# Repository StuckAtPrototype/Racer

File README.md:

# Micro Racer Car - StuckAtPrototype

*thank you for the overwhelmingly positve support!! such an inspiration to keep making fun open source content!*

## New Youtube video about improvements 
Lots of new improvements and I am now selling a kit for these! Check out the video here:
https://www.youtube.com/watch?v=FulhEs5R5WU

## Original Youtube Video
A bit of a back-story of how this project came to be. 

Sub if you like what you see.

*Some pictures of the project*

## Hardware Remote for this car

https://github.com/StuckAtPrototype/Thumbtroller

## Project Structure
The project consists of
1. Firmware
2. Hardware
3. Mechanical 
4. Scripts

These are structured into their own files. I could have used submodules, but decided against it.  

### 1. Firmware
Code for the little car. This lives on the ESP32

#### Requirements
- ESP32 IDF version 5.3.1
- USB to Serial dongle
- Target set to ESP32-H2

### 2. Hardware

#### Schematic
PDF schematic included for your viewing pleasure. 
#### PCBs
All the gerber files you'd need to send to a fab house. 
#### Kicad
All the files you'd need to expand and work on this further. If you'd like. 

### 3. Mechanical

#### Enclosure
All the step files you need to make one of these. Extrusion printer works well for this part.  

#### Wheels
A bit of caution on this one.. you'll need an SLA printer. 

### 4. Scripts
Did anyone say neural networks? 

This folder has all the python code you'd need to train up your own neural network for the car. It also consists scripts that let you drive it using a keyboard -- just in case you dont want to make a physical controller.  

#### Requirements
- Python 3
- You'll need to install a bunch of pip modules 

#### Training the neural network
Training the neural network is as simple as running the training script with the data in the `color_data.txt` file. For data format see the sample data in the file. You need to stick to the formatting. 

To train run `python trainer.py`

#### Keyboard controller
To run the script `python controller.py`

Use `w` `s` `a` `d` for control. Modify the script for different speeds, etc

*Protocol for motor control* 

60,1,60,1,5 -- translates to:

motor side A: speed 60, direction forward

motor side B: speed 60, direction forward

500 miliseconds run time

See firmware file `motor.c` if you need more details

## What the project could use
1. Cleanup, but thats true for almost anything out there
2. Some fun code that makes the little car drive using the color sensor -- think very fancy line follower
3. LLM integration -- ChatGPT driving a physical little robot? anyone? :)

## If you take it further
Let me know if you ever make one of these, I'd love to see it. Seriously, that'd be exciting and inspiring to keep making my projects open source!

---
## License
### Apache 2.0 -- i.e. use as you'd like
http://www.apache.org/licenses/LICENSE-2.0

--- 
## Special Thanks
Thanks to Michael Angerer for his open sourced `esp32_ble_ota` project. I used it to get BLE running in this project. His blog post and github repo are a great resource. Check it out. https://github.com/michael-angerer/esp32_ble_ota

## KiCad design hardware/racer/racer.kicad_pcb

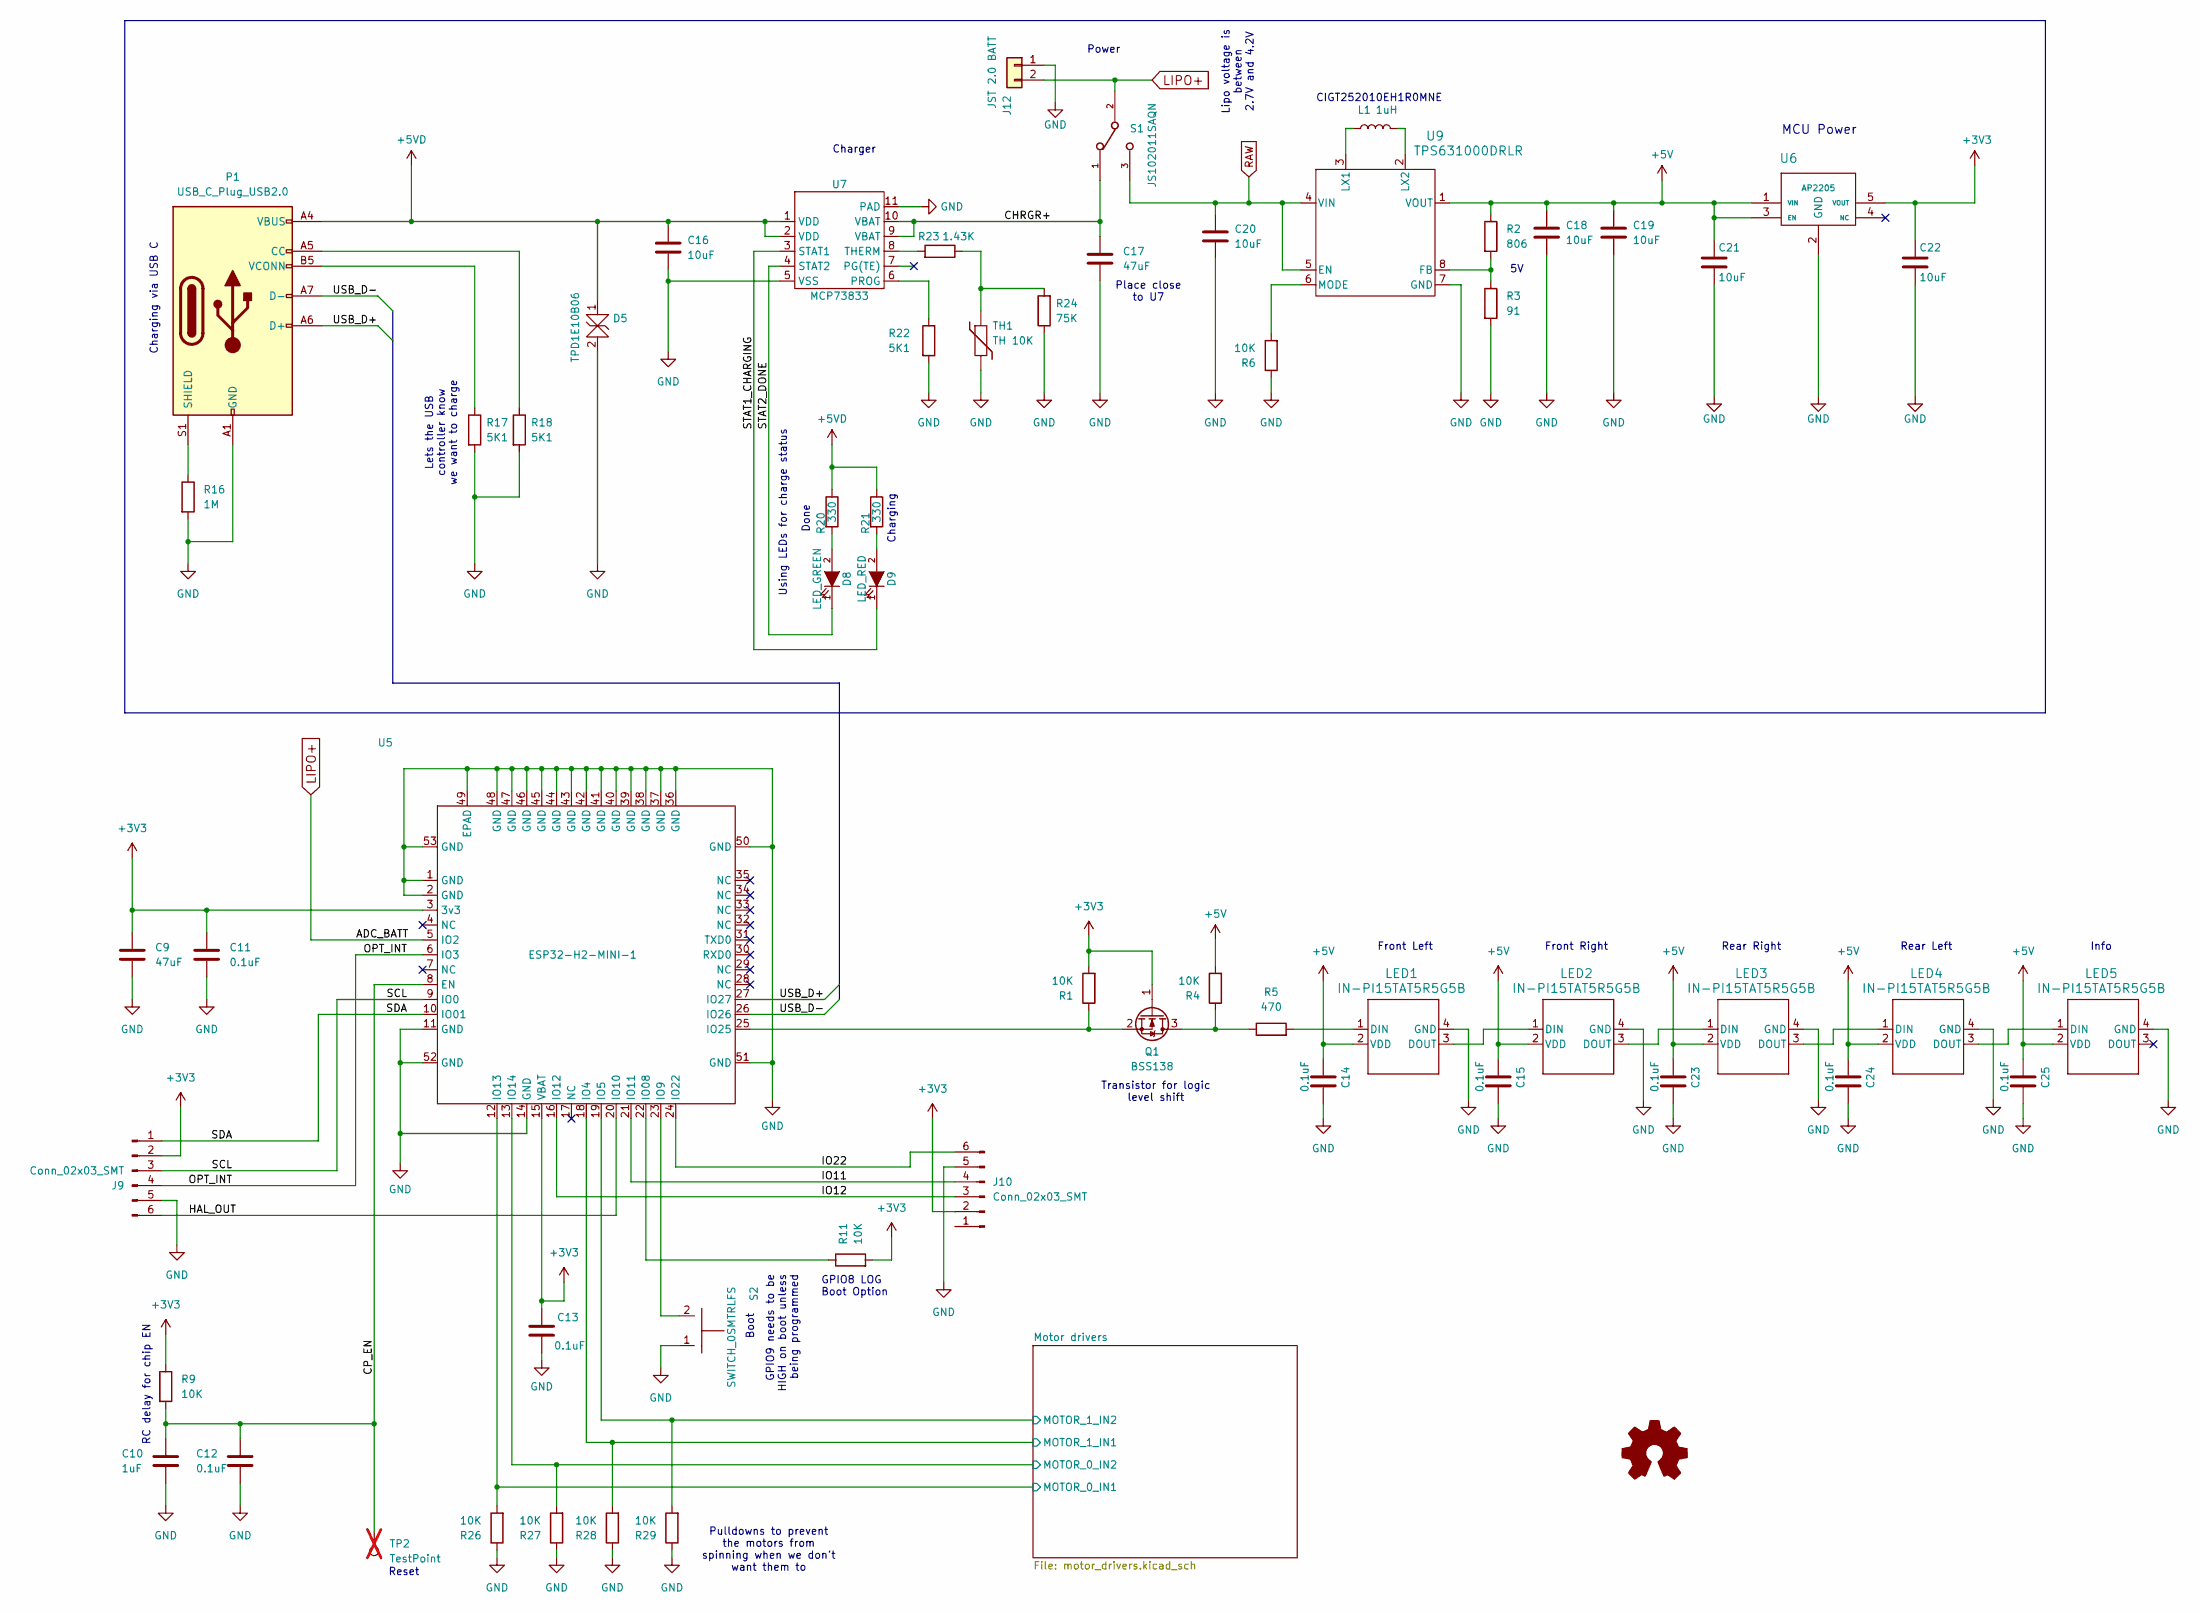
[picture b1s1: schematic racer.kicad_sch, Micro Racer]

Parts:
C9, C17: 47uF; C_0603_1608Metric
C10: 1uF; C_0603_1608Metric
C11, C12, C13, C14, C15, C23, C24, C25: 0.1uF; C_0603_1608Metric
C16, C18, C19, C20, C21, C22: 10uF; C_0603_1608Metric
D5: TPD1E10B06; D_SOD-523
D8: LED_GREEN; C_0603_1608Metric
D9: LED_RED; C_0603_1608Metric
J9, J10: Conn_02x03_SMT; PinHeader_2x03_P1.27mm_Vertical_SMD
J12: JST 2.0 BATT; JST_PH_B2B-PH-K_1x02_P2.00mm_Vertical
L1: 1uH; RES_CIGT252010
LED1, LED2, LED3, LED4, LED5: IN-PI15TAT5R5G5B; IN-PI15_INL
P1: USB_C_Plug_USB2.0; GCT_USB4105-GF-A
Q1: BSS138; SOT-23
R1, R4, R6, R9, R11, R26, R27, R28, R29: 10K; R_0603_1608Metric
R2: 806; R_0603_1608Metric
R3: 91; R_0603_1608Metric
R5: 470; R_0603_1608Metric
R16: 1M; R_0603_1608Metric
R17, R18, R22: 5K1; R_0603_1608Metric
R20, R21: 330; R_0603_1608Metric
R23: 1.43K; R_0603_1608Metric
R24: 75K; R_0603_1608Metric
S1: JS102011SAQN; SW_JS102011SAQN
S2: SWITCH_0SMTRLFS
TH1: TH 10K; R_0603_1608Metric
TP2: TestPoint; TestPoint_Pad_1.5x1.5mm; not fitted
U5: ESP32-H2-MINI-1; MODULE_ESP32-H2-MINI-1-H2
U6: AP2205; AP2204
U7: MCP73833; SON50P300X300X100-11N
U9: TPS631000DRLR; TPS631000DRLR_TEX

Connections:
+3V3: C9.1, C11.1, C13.1, C22.1, J9.2, J10.2, Q1.1 (G), R1.2, R9.1, R11.2, U5.3 (3v3), U5.15 (VBAT), U6.5 (VOUT)
+5V: C14.1, C15.1, C18.1, C19.1, C21.1, C23.1, C24.1, C25.1, LED1.2 (VDD), LED2.2 (VDD), LED3.2 (VDD), LED4.2 (VDD), LED5.2 (VDD), R2.1, R4.2, U6.1 (VIN), U6.3 (EN), U9.1 (VOUT)
+5VD: C16.1, D5.1, P1.A4 (VBUS), P1.A9 (VBUS), P1.B4 (VBUS), P1.B9 (VBUS), R20.1, R21.1, U7.1 (VDD), U7.2 (VDD)
/CHRGR+: C17.1, S1.1, U7.9 (VBAT), U7.10 (VBAT)
/CP_EN: C10.1, C12.1, R9.2, TP2.1, U5.8 (EN)
/HAL_OUT: J9.6, U5.20 (IO10)
/IO11: J10.4, U5.21 (IO11)
/IO12: J10.3, U5.16 (IO12)
/IO22: J10.6, U5.24 (IO22)
/OPT_INT: J9.4, U5.6 (IO3)
/SCL: J9.3, U5.9 (IO0)
/SDA: J9.1, U5.10 (IO01)
/STAT1_CHARGING: D9.1 (K), U7.3 (STAT1)
/STAT2_DONE: D8.1 (K), U7.4 (STAT2)
/USB_D+: P1.A6 (D+), U5.27 (IO27)
/USB_D-: P1.A7 (D-), U5.26 (IO26)
GND: C9.2, C10.2, C11.2, C12.2, C13.2, C14.2, C15.2, C16.2, C17.2, C18.2, C19.2, C20.2, C21.2, C22.2, C23.2, C24.2, C25.2, D5.2, J9.5, J10.5, J12.1, LED1.4 (GND), LED2.4 (GND), LED3.4 (GND), LED4.4 (GND), LED5.4 (GND), P1.A1 (GND), P1.A12 (GND), P1.B1 (GND), P1.B12 (GND), R3.2, R6.1, R16.2, R17.2, R18.2, R22.2, R24.1, R26.1, R27.1, R28.1, R29.1, S2.1, TH1.2, U5.1 (GND), U5.2 (GND), U5.11 (GND), U5.14 (GND), U5.36 (GND), U5.37 (GND), U5.38 (GND), U5.39 (GND), U5.40 (GND), U5.41 (GND), U5.42 (GND), U5.43 (GND), U5.44 (GND), U5.45 (GND), U5.46 (GND), U5.47 (GND), U5.48 (GND), U5.49 (EPAD), U5.50 (GND), U5.51 (GND), U5.52 (GND), U5.53 (GND), U6.2 (GND), U7.5 (VSS), U7.11 (PAD), U9.7 (GND); also elsewhere on the board
LIPO+: J12.2, S1.2, U5.5 (IO2)
MOTOR_0_IN1: R26.2, U5.12 (IO13); also elsewhere on the board
MOTOR_0_IN2: R27.2, U5.13 (IO14); also elsewhere on the board
MOTOR_1_IN1: R28.2, U5.18 (IO4); also elsewhere on the board
MOTOR_1_IN2: R29.2, U5.19 (IO5); also elsewhere on the board
unnamed: D8.2 (A), R20.2
unnamed: D9.2 (A), R21.2
unnamed: LED1.1 (DIN), R5.2
unnamed: LED1.3 (DOUT), LED2.1 (DIN)
unnamed: LED2.3 (DOUT), LED3.1 (DIN)
unnamed: LED3.3 (DOUT), LED4.1 (DIN)
unnamed: LED4.3 (DOUT), LED5.1 (DIN)
unnamed: P1.A5 (CC), R18.1
unnamed: P1.S1 (SHIELD), R16.1
unnamed: P1.B5 (VCONN), R17.1
unnamed: Q1.3 (D), R4.1, R5.1
unnamed: Q1.2 (S), R1.1, U5.25 (IO25)
unnamed: R23.1, R24.2, TH1.1
unnamed: R11.1, U5.22 (IO08)
unnamed: S2.2, U5.23 (IO9)
unnamed: R22.1, U7.6 (PROG)
unnamed: R23.2, U7.8 (THERM)
unnamed: R2.2, R3.1, U9.8 (FB)
unnamed: L1.1, U9.3 (LX1)
unnamed: L1.2, U9.2 (LX2)
unnamed: R6.2, U9.6 (MODE)
RAW: C20.1, S1.3, U9.4 (VIN), U9.5 (EN); also elsewhere on the board

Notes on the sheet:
Lipo voltage is between 2.7V and 4.2V
Charging via USB C
Using LEDs for charge status
RC delay for chip EN
Lets the USB controller know we want to charge
Front Right
Power
Rear Right
Reset
GPIO9 needs to be HIGH on boot unless being programmed
Pulldowns to prevent the motors from spinning when we don't want them to
Charger
GPIO8 LOG Boot Option
Charging
Done
Info
MCU Power
Front Left
CIGT252010EH1R0MNE
Rear Left
Place close to U7
Boot
Transistor for logic level shift

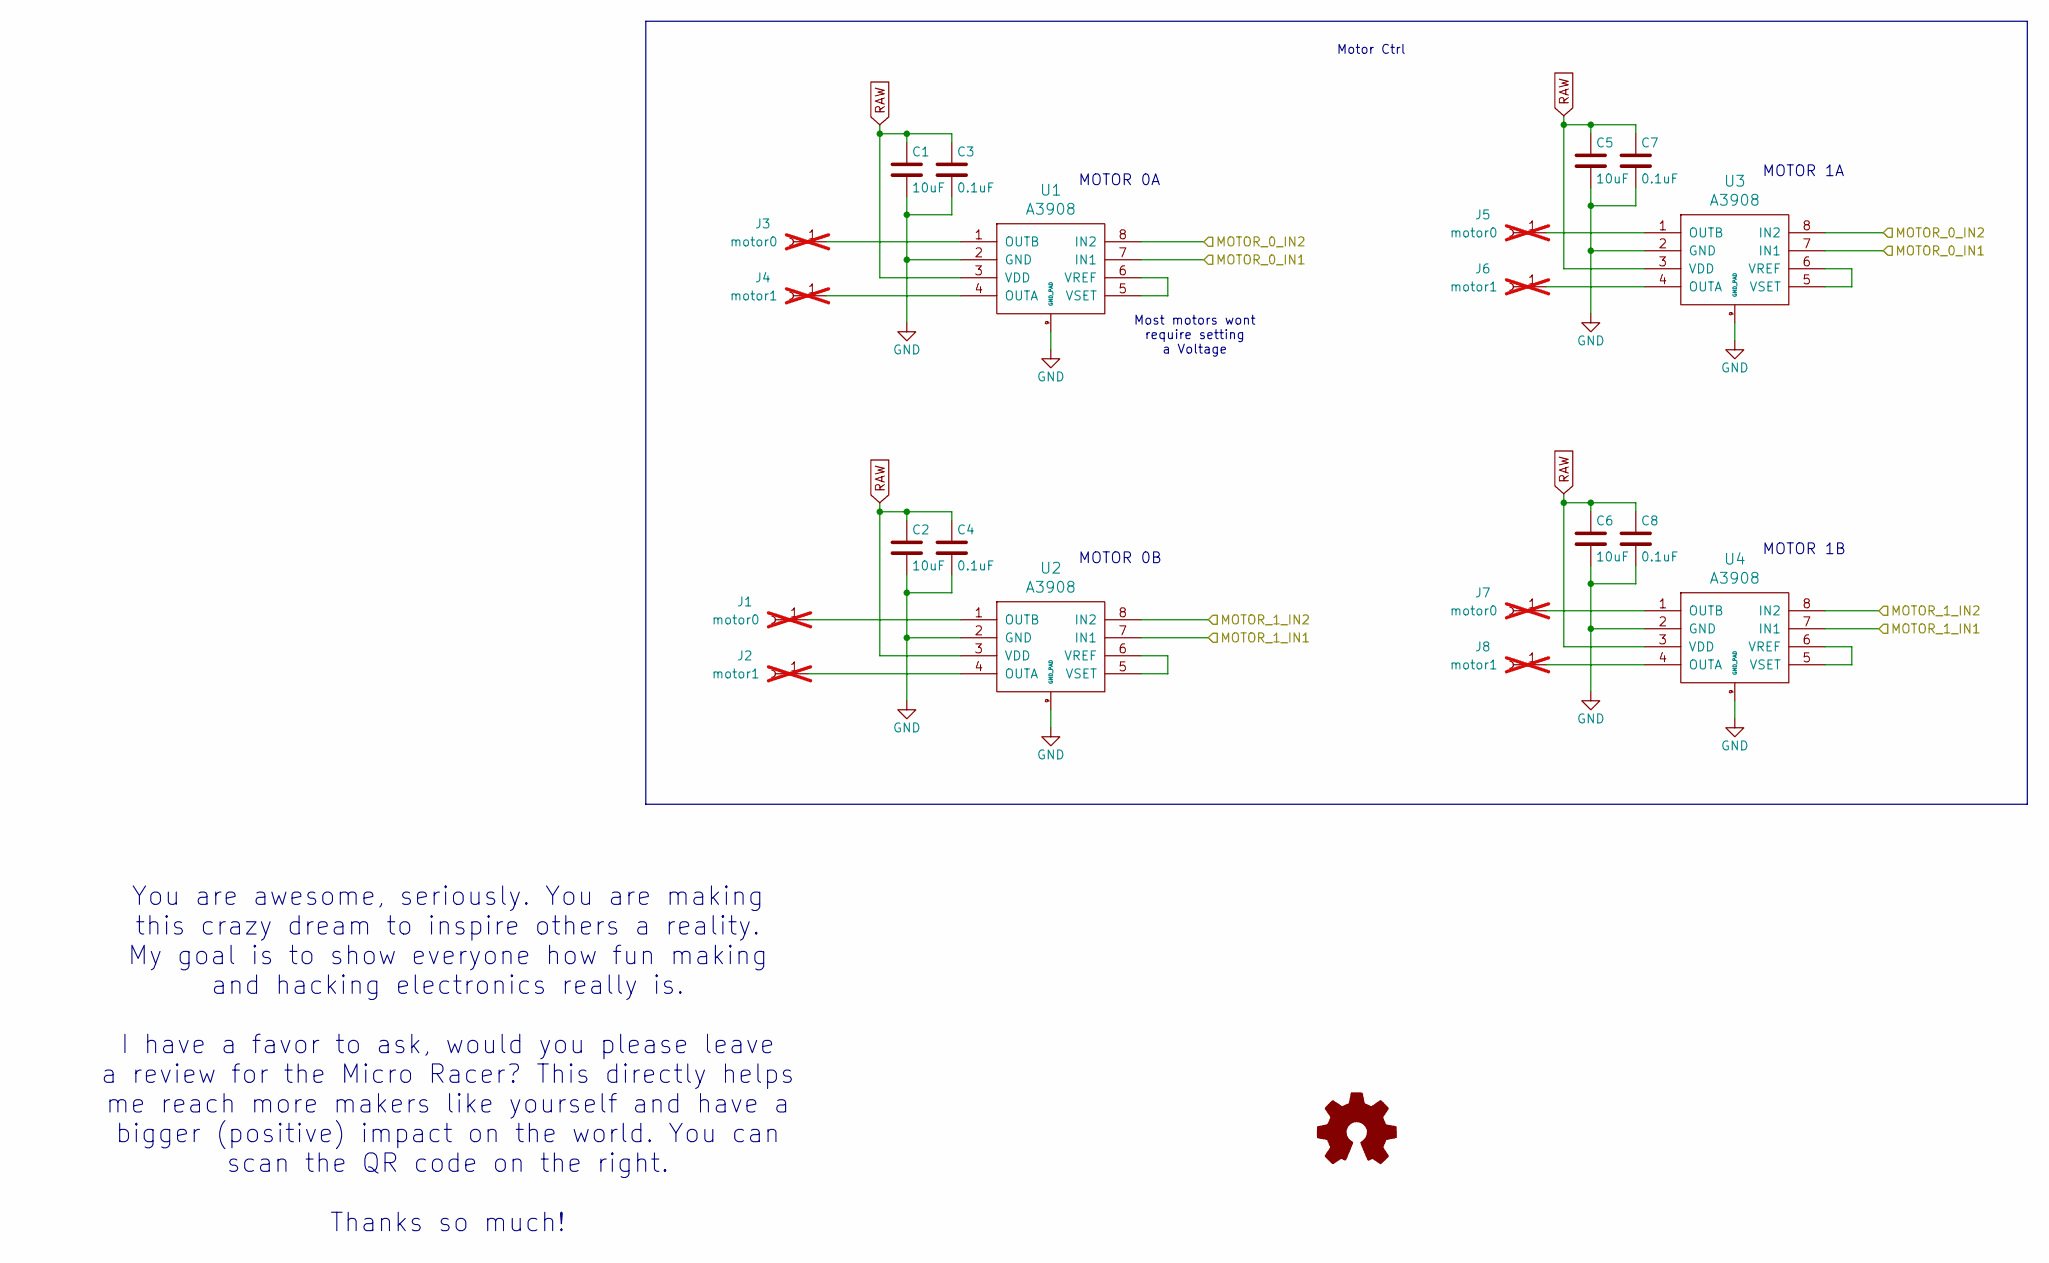
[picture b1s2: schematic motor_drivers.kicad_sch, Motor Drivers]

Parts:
C1, C2, C5, C6: 10uF; C_0603_1608Metric
C3, C4, C7, C8: 0.1uF; C_0603_1608Metric
J1, J3, J5, J7: motor0; TestPoint_Pad_2.0x2.0mm; not fitted
J2, J4, J6, J8: motor1; TestPoint_Pad_2.0x2.0mm; not fitted
U1, U2, U3, U4: A3908

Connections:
GND: C1.2, C2.2, C3.2, C4.2, C5.2, C6.2, C7.2, C8.2, U1.2 (GND), U1.9 (GND_PAD), U2.2 (GND), U2.9 (GND_PAD), U3.2 (GND), U3.9 (GND_PAD), U4.2 (GND), U4.9 (GND_PAD); also elsewhere on the board
MOTOR_0_IN1: U1.7 (IN1), U3.7 (IN1); also elsewhere on the board
MOTOR_0_IN2: U1.8 (IN2), U3.8 (IN2); also elsewhere on the board
MOTOR_1_IN1: U2.7 (IN1), U4.7 (IN1); also elsewhere on the board
MOTOR_1_IN2: U2.8 (IN2), U4.8 (IN2); also elsewhere on the board
unnamed: J1.1, U2.1 (OUTB)
unnamed: J2.1, U2.4 (OUTA)
unnamed: J3.1, U1.1 (OUTB)
unnamed: J4.1, U1.4 (OUTA)
unnamed: J5.1, U3.1 (OUTB)
unnamed: J6.1, U3.4 (OUTA)
unnamed: J7.1, U4.1 (OUTB)
unnamed: J8.1, U4.4 (OUTA)
unnamed: U1.5 (VSET), U1.6 (VREF)
unnamed: U2.5 (VSET), U2.6 (VREF)
unnamed: U3.5 (VSET), U3.6 (VREF)
unnamed: U4.5 (VSET), U4.6 (VREF)
RAW: C1.1, C2.1, C3.1, C4.1, C5.1, C6.1, C7.1, C8.1, U1.3 (VDD), U2.3 (VDD), U3.3 (VDD), U4.3 (VDD); also elsewhere on the board

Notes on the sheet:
Most motors wont require setting a Voltage
You are awesome, seriously. You are making this crazy dream to inspire others a reality. My goal is to show everyone how fun making and hacking electronics really is. I have a favor to ask, would you please leave a review for the Micro Racer? This directly helps me reach more makers like yourself a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
MOTOR 1B
MOTOR 0A
Motor Ctrl
MOTOR 1A
MOTOR 0B

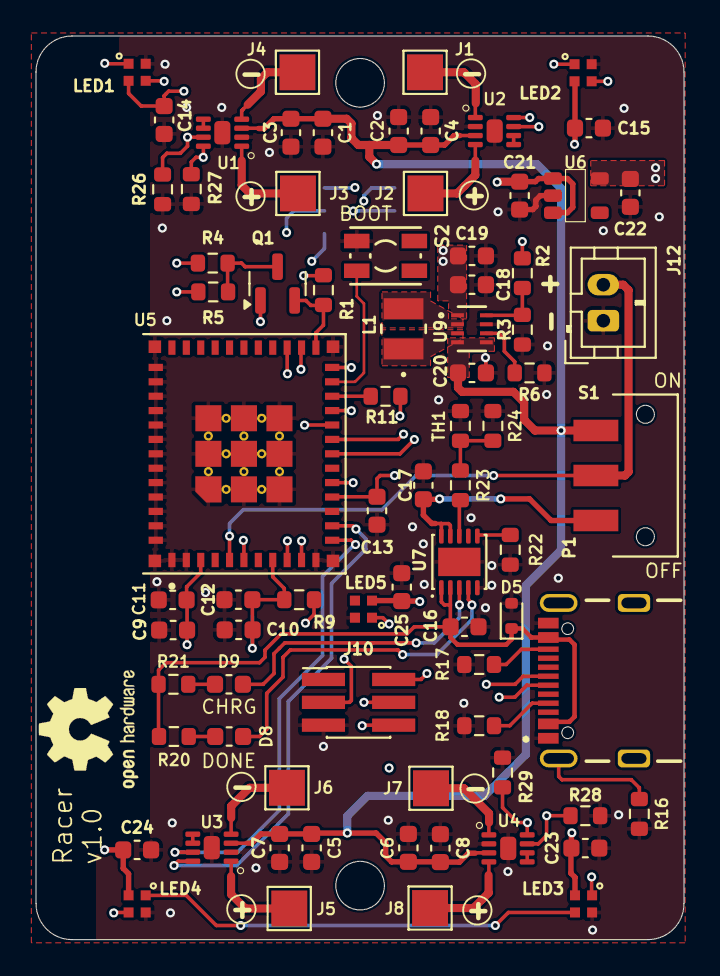
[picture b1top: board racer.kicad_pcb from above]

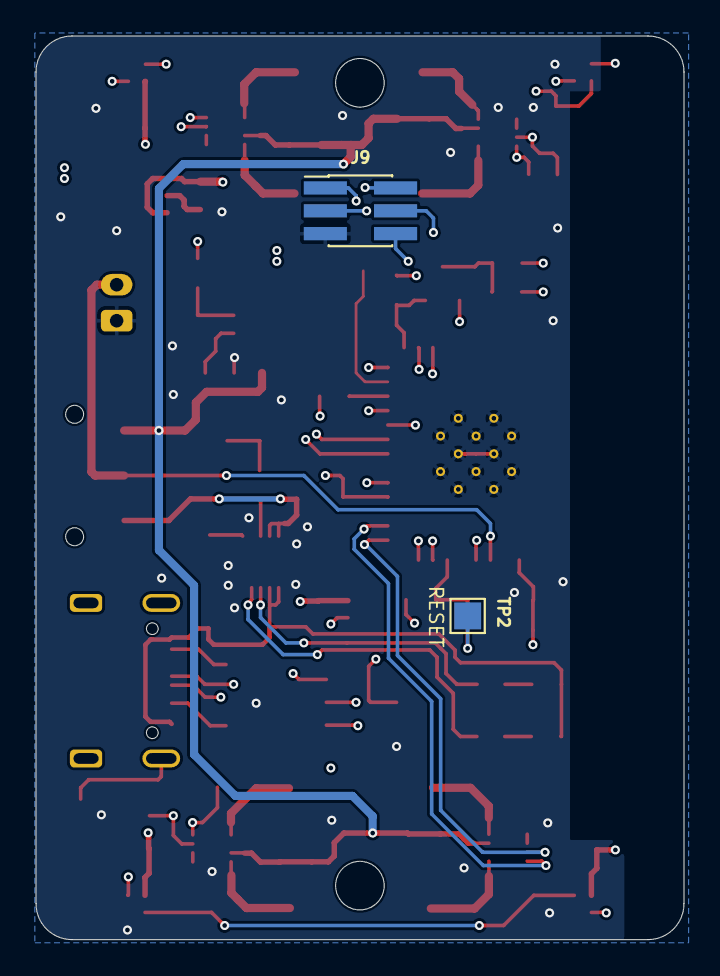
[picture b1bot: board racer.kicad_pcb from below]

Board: 4 copper layers, 36.0 x 50.2 mm, 79 parts (2 on the bottom side), 56 nets.

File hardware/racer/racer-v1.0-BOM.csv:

Designator,Quantity,Manufacturer Part Number,Package/Footprint,Description
U9,1,TPS631000DRLR,TPS631000DRLR_TEX,TPS631000DRLR
"R6,R26,R28,R29,R9,R1,R27,R11,R4",9,WR06X103 JTL,R_0603_1608Metric,10K
"C2,C16,C20,C18,C5,C6,C19,C1,C22",9,GRM188R61A106ME69D,C_0603_1608Metric,10uF
S2,1,RKB2SJK250SMTR LFS,SWITCH_0SMTRLFS,SWITCH_0SMTRLFS
"C7,C12,C13,C24,C15,C3,C8,C14,C4,C23,C11,C25",12,CC0603KRX7R7BB104,C_0603_1608Metric,0.1uF
R2,1,RQ73C1J806RBTDF,R_0603_1608Metric,806
U6,1,AP2205-33W5-7,AP2204,AP2205
R23,1,RT0603BRE071K43L,R_0603_1608Metric,1.43K
J9,1,GRPB032VWQS-RC,PinHeader_2x03_P1.27mm_Vertical_SMD,Conn_02x03_SMT
Q1,1,BSS138,SOT-23,BSS138
D9,1,150060RS75000,C_0603_1608Metric,LED_RED
"R17,R22,R18",3,RC0603FR-075K1L,R_0603_1608Metric,5K1
"LED1,LED3,LED5,LED4,LED2",5,IN-PI15TAT5R5G5B,IN-PI15_INL,IN-PI15TAT5R5G5B
D8,1,150060GS75000,C_0603_1608Metric,LED_GREEN
"U4,U1,U2,U3",4,A3908EEETR-T,A3908,A3908
J12,1,B2B-PH-K-S,JST_PH_B2B-PH-K_1x02_P2.00mm_Vertical,JST 2.0 BATT
P1,1,USB4105-GF-A,GCT_USB4105-GF-A,USB_C_Plug_USB2.0
TH1,1,NTCG163JF103HT1,R_0603_1608Metric,TH 10K
U5,1,ESP32-H2-MINI-1,MODULE_ESP32-H2-MINI-1-H2,ESP32-H2-MINI-1
R3,1,CR0603-FX-91R0ELF ,R_0603_1608Metric,91
R5,1,ESR03EZPF4700,R_0603_1608Metric,470
L1,1,CIGT252010EH1R0MNE,RES_CIGT252010,1uH
C10,1,CC0603KRX5R8BB105,C_0603_1608Metric,1uF
"R21,R20",2,RC0603JR-07330RL,R_0603_1608Metric,330
D5,1,TPD1E10B06DYAR,D_SOD-523,TPD1E10B06
S1,1,JS102011SAQN,SW_JS102011SAQN,JS102011SAQN
R24,1,ERJ-PB3B7502V,R_0603_1608Metric,75K
U7,1,MCP73833T-AMI/MF,SON50P300X300X100-11N,MCP73833
C17,1,GRM188R60J226MEA0J,C_0603_1608Metric,22uF
R16,1,RMCF0603FT1M00,R_0603_1608Metric,1M
C9,1,GRM188C80E476ME05D,C_0603_1608Metric,47uF
C21,1,CL10A225KO8NNNC,C_0603_1608Metric,2.2uF

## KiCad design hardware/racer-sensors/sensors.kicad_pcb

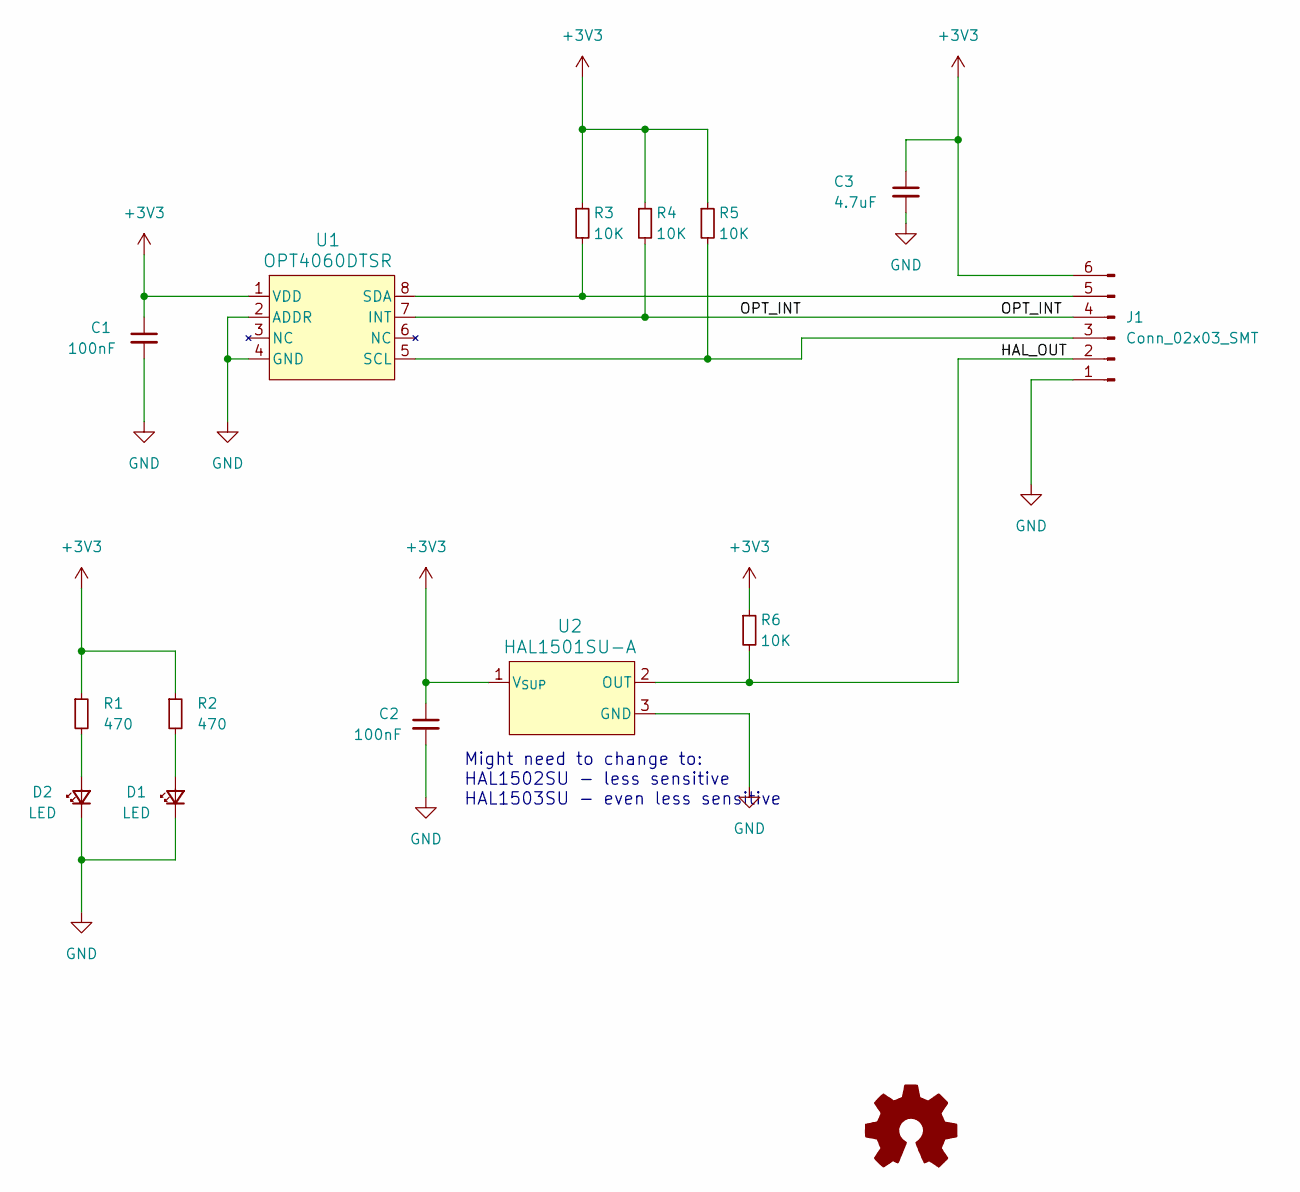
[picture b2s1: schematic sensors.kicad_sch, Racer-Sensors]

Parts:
C1, C2: 100nF; C_0603_1608Metric
C3: 4.7uF; C_0603_1608Metric
D1, D2: LED; LED_0603_1608Metric
J1: Conn_02x03_SMT; PinHeader_2x03_P1.27mm_Vertical_SMD
R1, R2: 470; R_0603_1608Metric
R3, R4, R5, R6: 10K; R_0603_1608Metric
U1: OPT4060DTSR; FCSOT8_DTS_TEX
U2: HAL1501SU-A; SOT-23_TO-236_TDK

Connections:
+3V3: C1.1, C2.1, C3.1, J1.6, R1.1, R2.1, R3.1, R4.1, R5.1, R6.1, U1.1 (VDD), U2.1 (VSUP)
/HAL_OUT: J1.2, R6.2, U2.2 (OUT)
/OPT_INT: J1.4, R4.2, U1.7 (INT)
/SCL: J1.3, R5.2, U1.5 (SCL)
/SDA: J1.5, R3.2, U1.8 (SDA)
GND: C1.2, C2.2, C3.2, D1.1 (K), D2.1 (K), J1.1, U1.2 (ADDR), U1.4 (GND), U2.3 (GND)
unnamed: D1.2 (A), R2.2
unnamed: D2.2 (A), R1.2

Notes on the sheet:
Might need to change to: HAL1502SU - less sensitive HAL1503SU - even less sensitive

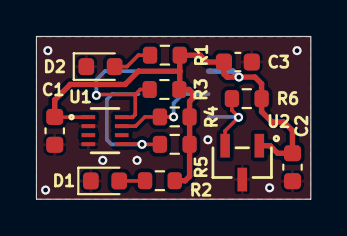
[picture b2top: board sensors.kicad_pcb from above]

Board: 4 copper layers, 15.2 x 9.0 mm, 14 parts (1 on the bottom side), 8 nets.

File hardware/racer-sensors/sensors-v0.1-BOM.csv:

Id,Designator,Footprint,Quantity,Designation,Supplier and ref,Notes
1,"R4,R5,R6,R3",R_0603_1608Metric,4,10K,WR06X103 JTL,
2,"D1,D2",LED_0603_1608Metric,2,LED,IN-S63AT5UW,
3,"R2,R1",R_0603_1608Metric,2,R,ESR03EZPF4700,"Note: I used a 470ohm resistor, but this might need to be adjusted to vary brightness "
4,C3,C_0603_1608Metric,1,4.7uF,GRM188R61A106ME69D,Replaced with 10uF
5,"C1,C2",C_0603_1608Metric,2,0.1uF,CC0603KRX7R7BB104,
6,U2,SOT-23_TO-236_TDK,1,HAL1501SU-A,HAL1501SU-A,
7,U1,FCSOT8_DTS_TEX,1,OPT4060DTSR,OPT4060DTSR,
8,J1,PinHeader_2x03_P1.27mm_Vertical_SMD,1,Conn_02x03_SMT,20021321-00006C4LF,

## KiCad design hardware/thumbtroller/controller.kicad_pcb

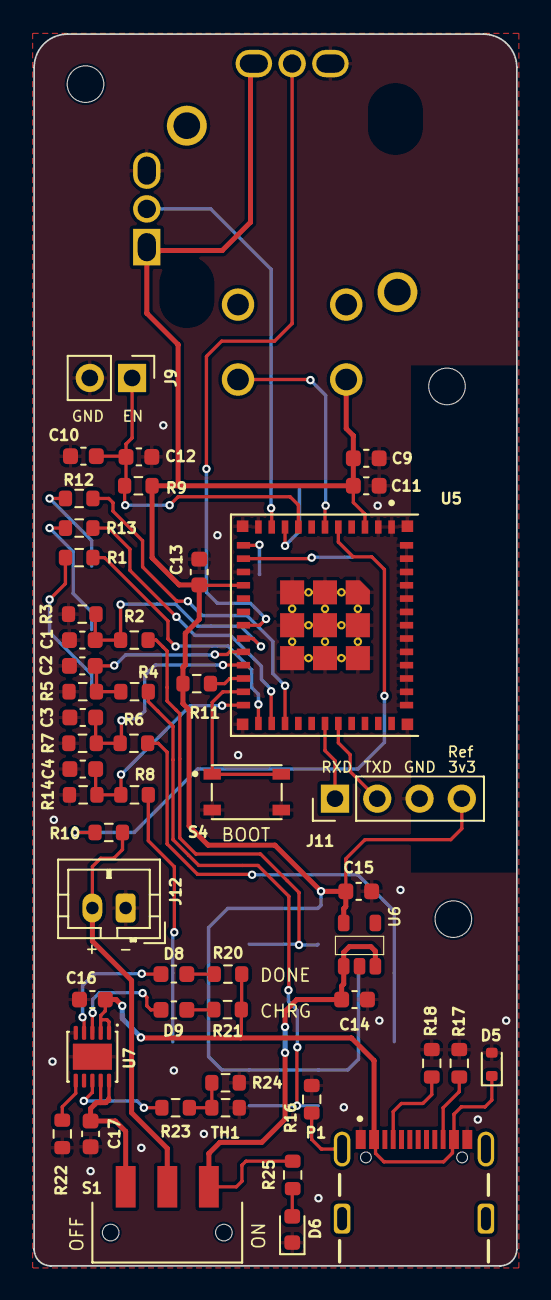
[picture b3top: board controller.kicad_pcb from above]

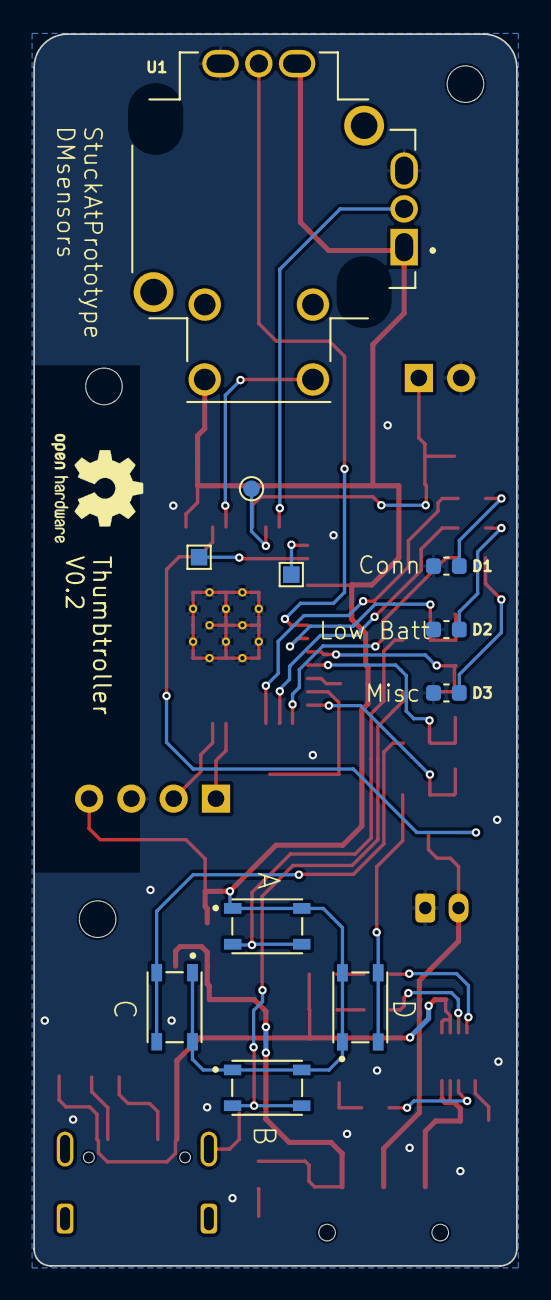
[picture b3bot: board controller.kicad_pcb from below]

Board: 4 copper layers, 29.0 x 74.0 mm, 61 parts (11 on the bottom side), 43 nets.

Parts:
C1, C2, C3, C4, C10: 1uF 25V; C_0603_1608Metric
C9: 47uF; C_0603_1608Metric
C11, C12, C13: 0.1uF; C_0603_1608Metric
C14: 2.2uF; C_0603_1608Metric
C15, C16: 10uF; C_0603_1608Metric
C17: 22uF; C_0603_1608Metric
D1, D2, D3, D8, D9: LED; C_0603_1608Metric
D5: TPD1E10B06DPYR; D_SOD-523
D6: PWLED; D_0603_1608Metric
J9: Chip Enable; PinHeader_1x02_P2.54mm_Vertical
J11: UART; PinHeader_1x04_P2.54mm_Vertical
J12: JST 2.0 BATT; JST_PH_B2B-PH-K_1x02_P2.00mm_Vertical
P1: USB_C_Plug_USB2.0; GCT_USB4105-GF-A
R1, R12, R13, R25: 200; R_0603_1608Metric
R2, R4, R6, R8, R9, R10, R11: 10k; R_0603_1608Metric
R3, R5, R7, R14: 100k; R_0603_1608Metric
R16: 1M; R_0603_1608Metric
R17, R18: 5k1; R_0603_1608Metric
R20, R21: 470; R_0603_1608Metric
R22, R23: 1.43K; R_0603_1608Metric
R24: 75K; R_0603_1608Metric
S1: JS102011SAQN; SW_JS102011SAQN
S2, S3, S4, S5, S6: TL4100AF240QG_; SW_PTS810_SJM_250_SMTR_LFS
TH1: TH 10k; R_0603_1608Metric
TP1: 0_IN1; TestPoint_Pad_1.0x1.0mm
TP2: 0_IN2; TestPoint_Pad_1.0x1.0mm
TP3: TP; TestPoint_Pad_D1.0mm
U1: THB001P; CNK_THB001P
U5: ESP32-H2-MINI-1; MODULE_ESP32-H2-MINI-1-H2
U6: AP2204
U7: MCP73833; SON50P300X300X100-11N

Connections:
+3V3: C9.1, C11.1, C13.1, C15.1, J11.4, R9.1, R11.2, S2.1, S3.1, S5.1, S6.1, U1.C, U1.VR1_1, U1.VR2_1, U5.3 (3v3), U5.15 (VBAT), U6.5 (VOUT)
+5V: C16.1, D5.1, P1.A4 (VBUS), P1.A9 (VBUS), R20.1, R21.1, U7.1 (VDD), U7.2 (VDD)
/ADC_BATT: R10.2, U5.5 (IO2)
/CHRGR+: C17.1, S1.1, U7.9 (VBAT), U7.10 (VBAT)
/CP_EN: C10.1, C12.1, J9.1, R9.2, U5.8 (EN)
/STAT1: D9.1 (K), U7.3 (STAT1)
/STAT2: D8.1 (K), U7.4 (STAT2)
/SW_A: C1.1, R2.1, R3.1, U5.19 (IO5)
/SW_B: C2.1, R4.1, R5.1, U5.20 (IO10)
/SW_C: C3.1, R6.1, R7.1, U5.21 (IO11)
/SW_D: C4.1, R8.1, R14.1, U5.24 (IO22)
/U0RXD: J11.1, U5.30 (RXD0)
/U0TXD: J11.2, U5.31 (TXD0)
/VR1: U1.VR1_2, U5.10 (IO01)
/VR2: U1.VR2_2, U5.18 (IO4)
/VR_BTN: U1.D, U5.6 (IO3)
/raw_voltage: C14.1, R25.2, S1.3, U6.1 (VIN), U6.3 (EN)
GND: C1.2, C2.2, C3.2, C4.2, C9.2, C10.2, C11.2, C12.2, C13.2, C14.2, C15.2, C16.2, C17.2, D1.1 (K), D2.1 (K), D3.1 (K), D5.2, D6.1 (K), J9.2, J11.3, J12.1, P1.A1 (GND), P1.A12 (GND), R3.2, R5.2, R7.2, R14.2, R16.2, R17.2, R18.2, R22.2, R24.1, S4.2, TH1.2, U1.VR1_3, U1.VR2_3, U5.1 (GND), U5.2 (GND), U5.11 (GND), U5.14 (GND), U5.36 (GND), U5.37 (GND), U5.38 (GND), U5.39 (GND), U5.40 (GND), U5.41 (GND), U5.42 (GND), U5.43 (GND), U5.44 (GND), U5.45 (GND), U5.46 (GND), U5.47 (GND), U5.48 (GND), U5.49 (EPAD), U5.50 (GND), U5.51 (GND), U5.52 (GND), U5.53 (GND), U6.2 (GND), U7.5 (VSS), U7.11 (PAD)
LIPO+: J12.2, R10.1, S1.2
unnamed: D1.2 (A), R12.1
unnamed: D2.2 (A), R13.1
unnamed: D3.2 (A), R1.1
unnamed: D6.2 (A), R25.1
unnamed: D8.2 (A), R20.2
unnamed: D9.2 (A), R21.2
unnamed: P1.A5 (CC), R18.1
unnamed: P1.S1 (SHIELD), R16.1
unnamed: P1.B5 (VCONN), R17.1
unnamed: R2.2, S2.2
unnamed: R4.2, S3.2
unnamed: R6.2, S5.2
unnamed: R8.2, S6.2
unnamed: R23.1, R24.2, TH1.1
unnamed: TP3.1, U5.9 (IO0)
unnamed: R11.1, U5.22 (IO08)
unnamed: S4.1, U5.23 (IO9)
unnamed: TP1.1, U5.12 (IO13)
unnamed: TP2.1, U5.13 (IO14)
unnamed: R1.2, U5.25 (IO25)
unnamed: R13.2, U5.26 (IO26)
unnamed: R12.2, U5.27 (IO27)
unnamed: R22.1, U7.6 (PROG)
unnamed: R23.2, U7.8 (THERM)

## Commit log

2024-10-15 version 2.0
2024-10-18 adding racer v0.2 intial BOM
2024-10-18 added mechanical parts for the racer
2024-10-19 adding the BOM for the sensors PCB
2024-10-19 Schematic improvement & LCSC BOM
    - Schematic readability improvements.
    - Changed schematic symbols.
    - Changed to hierarchical schematic.
    - Added LCSC BOM for the available components.
2024-10-21 Create LICENSE
    adding standardized license file for better discovery
2024-10-24 hardware: racer.kicad_pcb: Add thickness property to font nodes
2024-10-24 hardware: racer.kicad_pcb: Use the correct schematic filename in 'sheetfile' property
2024-10-24 hardware: racer.kicad_pcb: Fix wrong value of R22
2024-10-24 hardware: Add .gitignore file temporary KiCad files
2024-10-24 hardware: racer.kicad_pro: Update project file
2024-10-24 hardware: sensors.kicad_pcb: Add thickness property to font nodes
2024-10-24 hardware: sensors.kicad_pcb: Fix values of R1 and R2
2024-10-24 hardware: controller.kicad_pcb: Add thickness property to font nodes
2024-10-26 Schematic readability update
    Updated Schematics to hierarchical, Schematic size to A4.
2024-11-03 adding the sdkconfig. Originally I added sdkconfig.ci instead of sdkconfig by accident
2024-11-06 Change USB_C_Plug symbol to Connector:USB_C_Receptacle_PowerOnly_6P
    The used footprint is 6-pin, so the symbol should have 6 pins to
2024-11-06 Update PCB from schematic
    fixes pad <-> pin assignment
2024-11-07 Add part numbers to schematic
    * Add property `MFR Part #`
    * Add property `LCSC`
2024-11-07 Rename field to MPN
2024-11-07 Update PCB
2024-11-16 Automation of production files
    This creates a github action that automatizes the generation of 3D Render, gerber files, BOM, etc.
    * Changed name of inner layers from InN --> InnerN
    * Created github action
    * Added Kibot yaml for every pcb
2024-12-08 feat: make 'youtube video' image more obvious
2024-12-20 patch: move youtube_preview image to repository
2025-07-02 new video link
2025-10-16 removing sdkconfig tracking. we are only supposed to track sdkconfig.defaults
2025-10-17 official firmware version 1.0
2025-10-17 version 1.0 of CAD files
2025-10-17 hardware version 1.0
2025-10-19 reduced gain on the color sensor to 16x to better accomodate variance in LED brightness and tightened the maximum allowed tolerance for color brackets
2025-10-22 fixing sdkconfig files
2026-02-01 adding a manual calibration method to compensate for motor differences
2026-02-01 stopped tracking sdkconfig and redid the sdkconfig.defaults for IDF v5.5.1
